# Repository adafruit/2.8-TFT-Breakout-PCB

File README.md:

# 2.8" TFT LCD Display Breakout PCBs
&nbsp; <br />
Click to view/purchase from the Adafruit Shop:
- [2.8" TFT LCD with Touchscreen Breakout Board w/MicroSD Socket - ILI9341](https://www.adafruit.com/product/1770)
- [2.8" 18-bit color TFT LCD with touchscreen breakout board - ILI9325](https://www.adafruit.com/product/335)

Add some jazz & pizazz to your project with a color touchscreen LCD. This TFT display is big (2.8" diagonal) bright (4 white-LED backlight) and colorful! 240x320 pixels with individual RGB pixel control, this has way more resolution than a black and white 128x64 display. As a bonus, this display has a resistive touchscreen attached to it already, so you can detect finger presses anywhere on the screen.

The ILI9325 screen has been discontinued, but the 2.8" ILI341 touchscreen breakout is nearly identical, having both an 8-bit and a SPI interface mode as well as a MicroSD card socket, all in the same form factor! 

Adafruit 2.8" 18-bit color TFT LCD displays with microSD card breakout

These are the Eagle CAD files for the Adafruit 2.8" 18-bit color TFT LCD display with microSD card breakouts:
  ----> https://www.adafruit.com/product/1770 (newer ILI9341 version)
  ----> https://www.adafruit.com/products/335 (older ILI9325 version)

### License

Adafruit invests time and resources providing this open source design, please support Adafruit and open-source hardware by [purchasing products from Adafruit](https://www.adafruit.com)!

All text above must be included in any redistribution

Designed by Limor Fried/Ladyada for Adafruit Industries.
Creative Commons Attribution/Share-Alike, all text above must be included in any redistribution. 
See license.txt for additional information.

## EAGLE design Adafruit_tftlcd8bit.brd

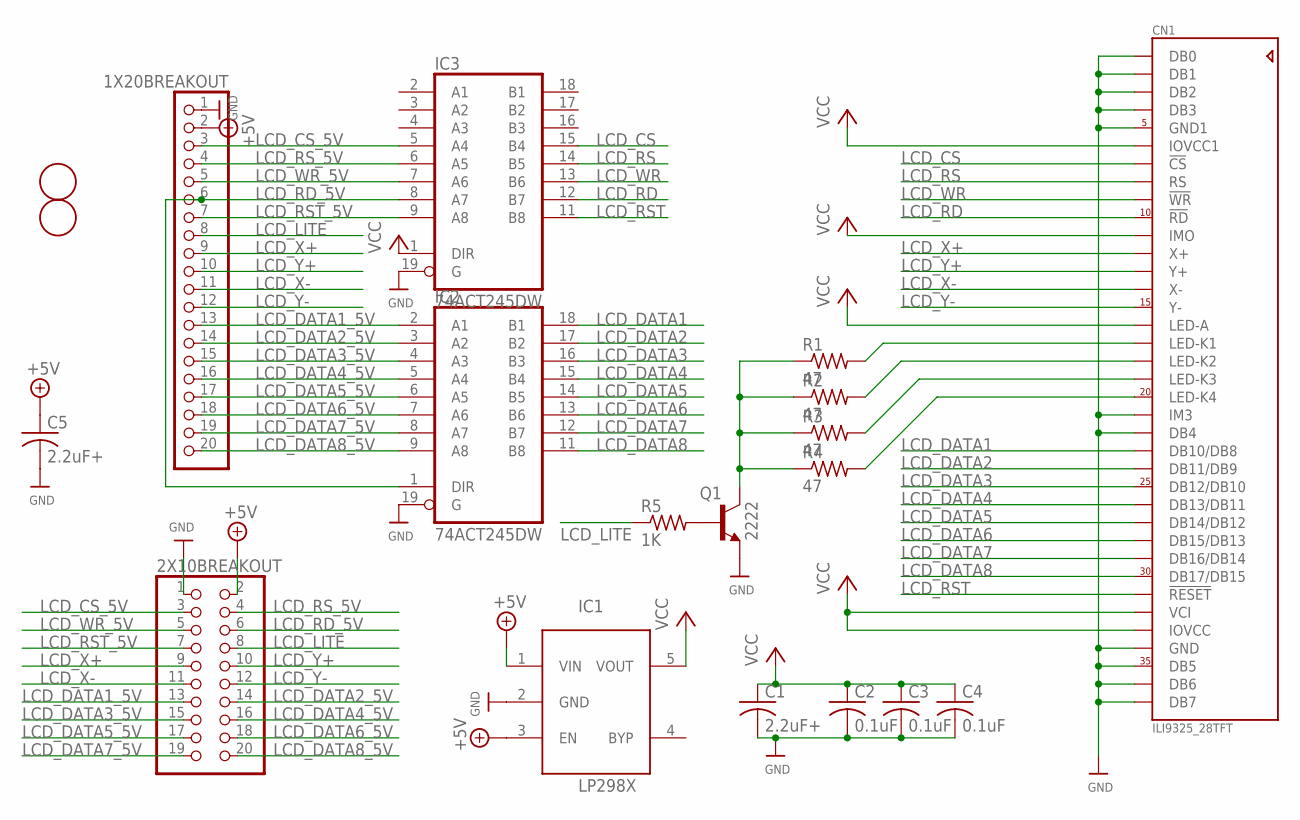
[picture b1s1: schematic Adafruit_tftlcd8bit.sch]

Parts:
1X20BREAKOUT: PINHD-1X20; 1X20
2X10BREAKOUT: PINHD-2X10; 2X10
C1, C5: 2.2uF+; C0805K
C2, C3, C4: 0.1uF; C0805K
CN1: ILI9325_28TFT; ILI9325_28INCH_TS
IC1: LP298XS; SOT23-5L
IC2, IC3: 74ACT245DW; SO20W
Q1: 2222; SOT23-BEC
R1, R2, R3, R4: 47; R0805
R5: 1K; R0805
U$9, U$11: FIDUCIAL; FIDUCIAL_1MM

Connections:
+5V: 1X20BREAKOUT.2, 2X10BREAKOUT.2, C5.1, IC1.1 (VIN), IC1.3 (EN)
GND: 1X20BREAKOUT.1, 2X10BREAKOUT.1, C1.2, C2.2, C3.2, C4.2, C5.2, CN1.1 (DB0), CN1.2 (DB1), CN1.3 (DB2), CN1.4 (DB3), CN1.5 (GND1), CN1.21 (IM3), CN1.22 (DB4), CN1.34 (GND), CN1.35 (DB5), CN1.36 (DB6), CN1.37 (DB7), IC1.2 (GND), IC2.10 (GND), IC2.19 (G), IC3.10 (GND), IC3.19 (G), Q1.E
LCD_CS: CN1.7 (!CS), IC3.15 (B4)
LCD_CS_5V: 1X20BREAKOUT.3, 2X10BREAKOUT.3, IC3.5 (A4)
LCD_DATA1: CN1.23 (DB10/DB8), IC2.18 (B1)
LCD_DATA1_5V: 1X20BREAKOUT.13, 2X10BREAKOUT.13, IC2.2 (A1)
LCD_DATA2: CN1.24 (DB11/DB9), IC2.17 (B2)
LCD_DATA2_5V: 1X20BREAKOUT.14, 2X10BREAKOUT.14, IC2.3 (A2)
LCD_DATA3: CN1.25 (DB12/DB10), IC2.16 (B3)
LCD_DATA3_5V: 1X20BREAKOUT.15, 2X10BREAKOUT.15, IC2.4 (A3)
LCD_DATA4: CN1.26 (DB13/DB11), IC2.15 (B4)
LCD_DATA4_5V: 1X20BREAKOUT.16, 2X10BREAKOUT.16, IC2.5 (A4)
LCD_DATA5: CN1.27 (DB14/DB12), IC2.14 (B5)
LCD_DATA5_5V: 1X20BREAKOUT.17, 2X10BREAKOUT.17, IC2.6 (A5)
LCD_DATA6: CN1.28 (DB15/DB13), IC2.13 (B6)
LCD_DATA6_5V: 1X20BREAKOUT.18, 2X10BREAKOUT.18, IC2.7 (A6)
LCD_DATA7: CN1.29 (DB16/DB14), IC2.12 (B7)
LCD_DATA7_5V: 1X20BREAKOUT.19, 2X10BREAKOUT.19, IC2.8 (A7)
LCD_DATA8: CN1.30 (DB17/DB15), IC2.11 (B8)
LCD_DATA8_5V: 1X20BREAKOUT.20, 2X10BREAKOUT.20, IC2.9 (A8)
LCD_LITE: 1X20BREAKOUT.8, 2X10BREAKOUT.8, R5.1
LCD_RD: CN1.10 (!RD), IC3.12 (B7)
LCD_RD_5V: 1X20BREAKOUT.6, 2X10BREAKOUT.6, IC2.1 (DIR), IC3.8 (A7)
LCD_RS: CN1.8 (RS), IC3.14 (B5)
LCD_RST: CN1.31 (!RESET), IC3.11 (B8)
LCD_RST_5V: 1X20BREAKOUT.7, 2X10BREAKOUT.7, IC3.9 (A8)
LCD_RS_5V: 1X20BREAKOUT.4, 2X10BREAKOUT.4, IC3.6 (A5)
LCD_WR: CN1.9 (!WR), IC3.13 (B6)
LCD_WR_5V: 1X20BREAKOUT.5, 2X10BREAKOUT.5, IC3.7 (A6)
LCD_X+: 1X20BREAKOUT.9, 2X10BREAKOUT.9, CN1.12 (X+)
LCD_X-: 1X20BREAKOUT.11, 2X10BREAKOUT.11, CN1.14 (X-)
LCD_Y+: 1X20BREAKOUT.10, 2X10BREAKOUT.10, CN1.13 (Y+)
LCD_Y-: 1X20BREAKOUT.12, 2X10BREAKOUT.12, CN1.15 (Y-)
unnamed: CN1.20 (LED-K4), R4.2
unnamed: CN1.17 (LED-K1), R1.2
unnamed: CN1.18 (LED-K2), R2.2
unnamed: CN1.19 (LED-K3), R3.2
unnamed: Q1.C, R1.1, R2.1, R3.1, R4.1
unnamed: Q1.B, R5.2
VCC: C1.1, C2.1, C3.1, C4.1, CN1.6 (IOVCC1), CN1.11 (IMO), CN1.16 (LED-A), CN1.32 (VCI), CN1.33 (IOVCC), IC1.5 (VOUT), IC2.20 (VCC), IC3.1 (DIR), IC3.20 (VCC)

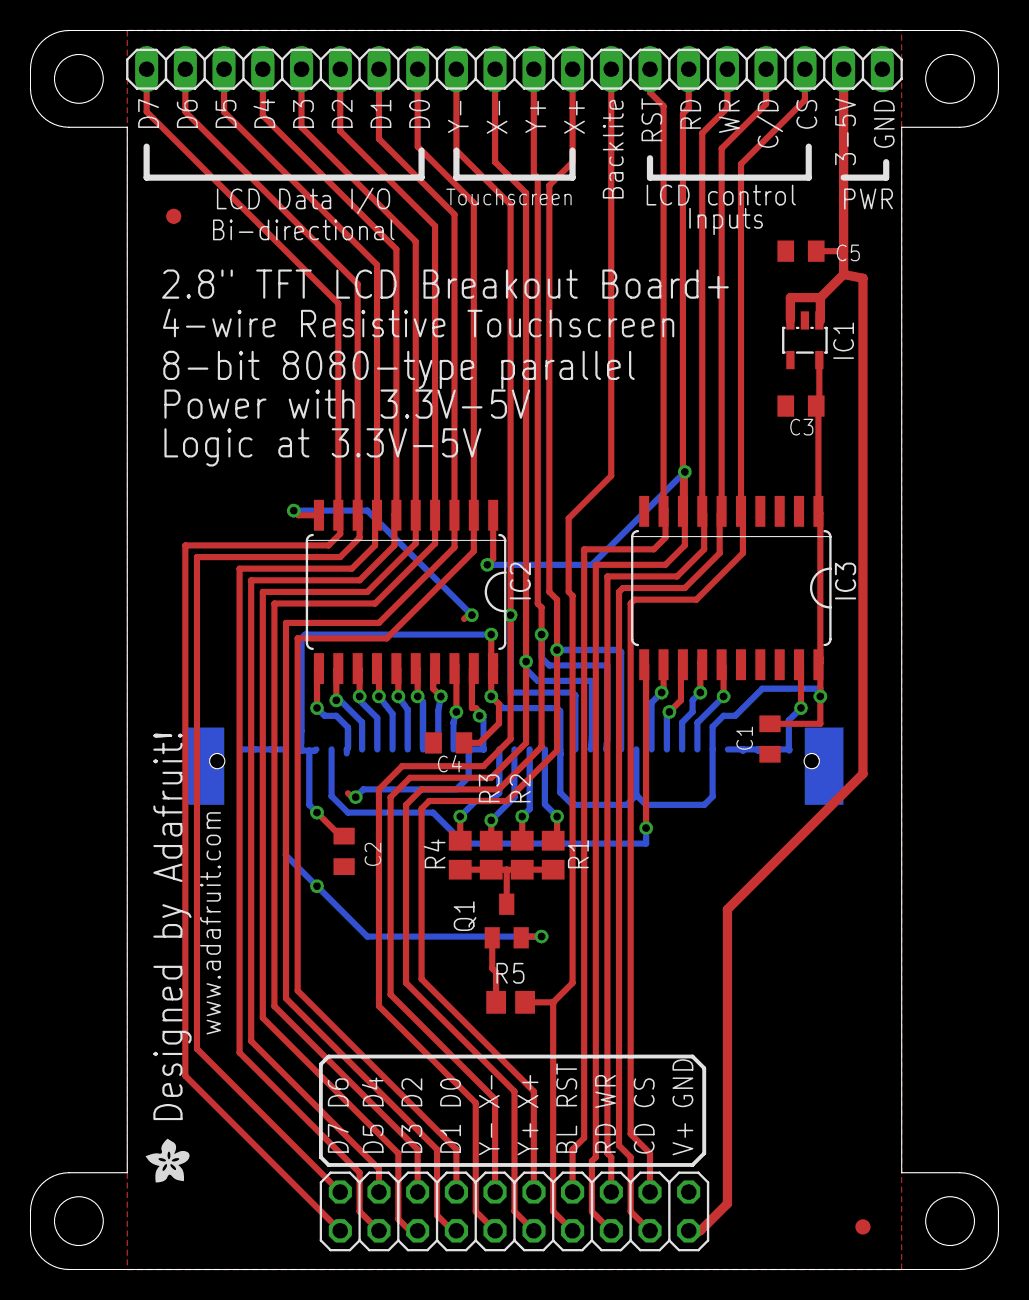
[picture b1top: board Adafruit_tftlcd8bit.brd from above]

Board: 2 copper layers, 63.5 x 81.3 mm, 20 parts (1 on the bottom side), 40 nets.

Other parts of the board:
U$3: ADAFRUIT200MIL

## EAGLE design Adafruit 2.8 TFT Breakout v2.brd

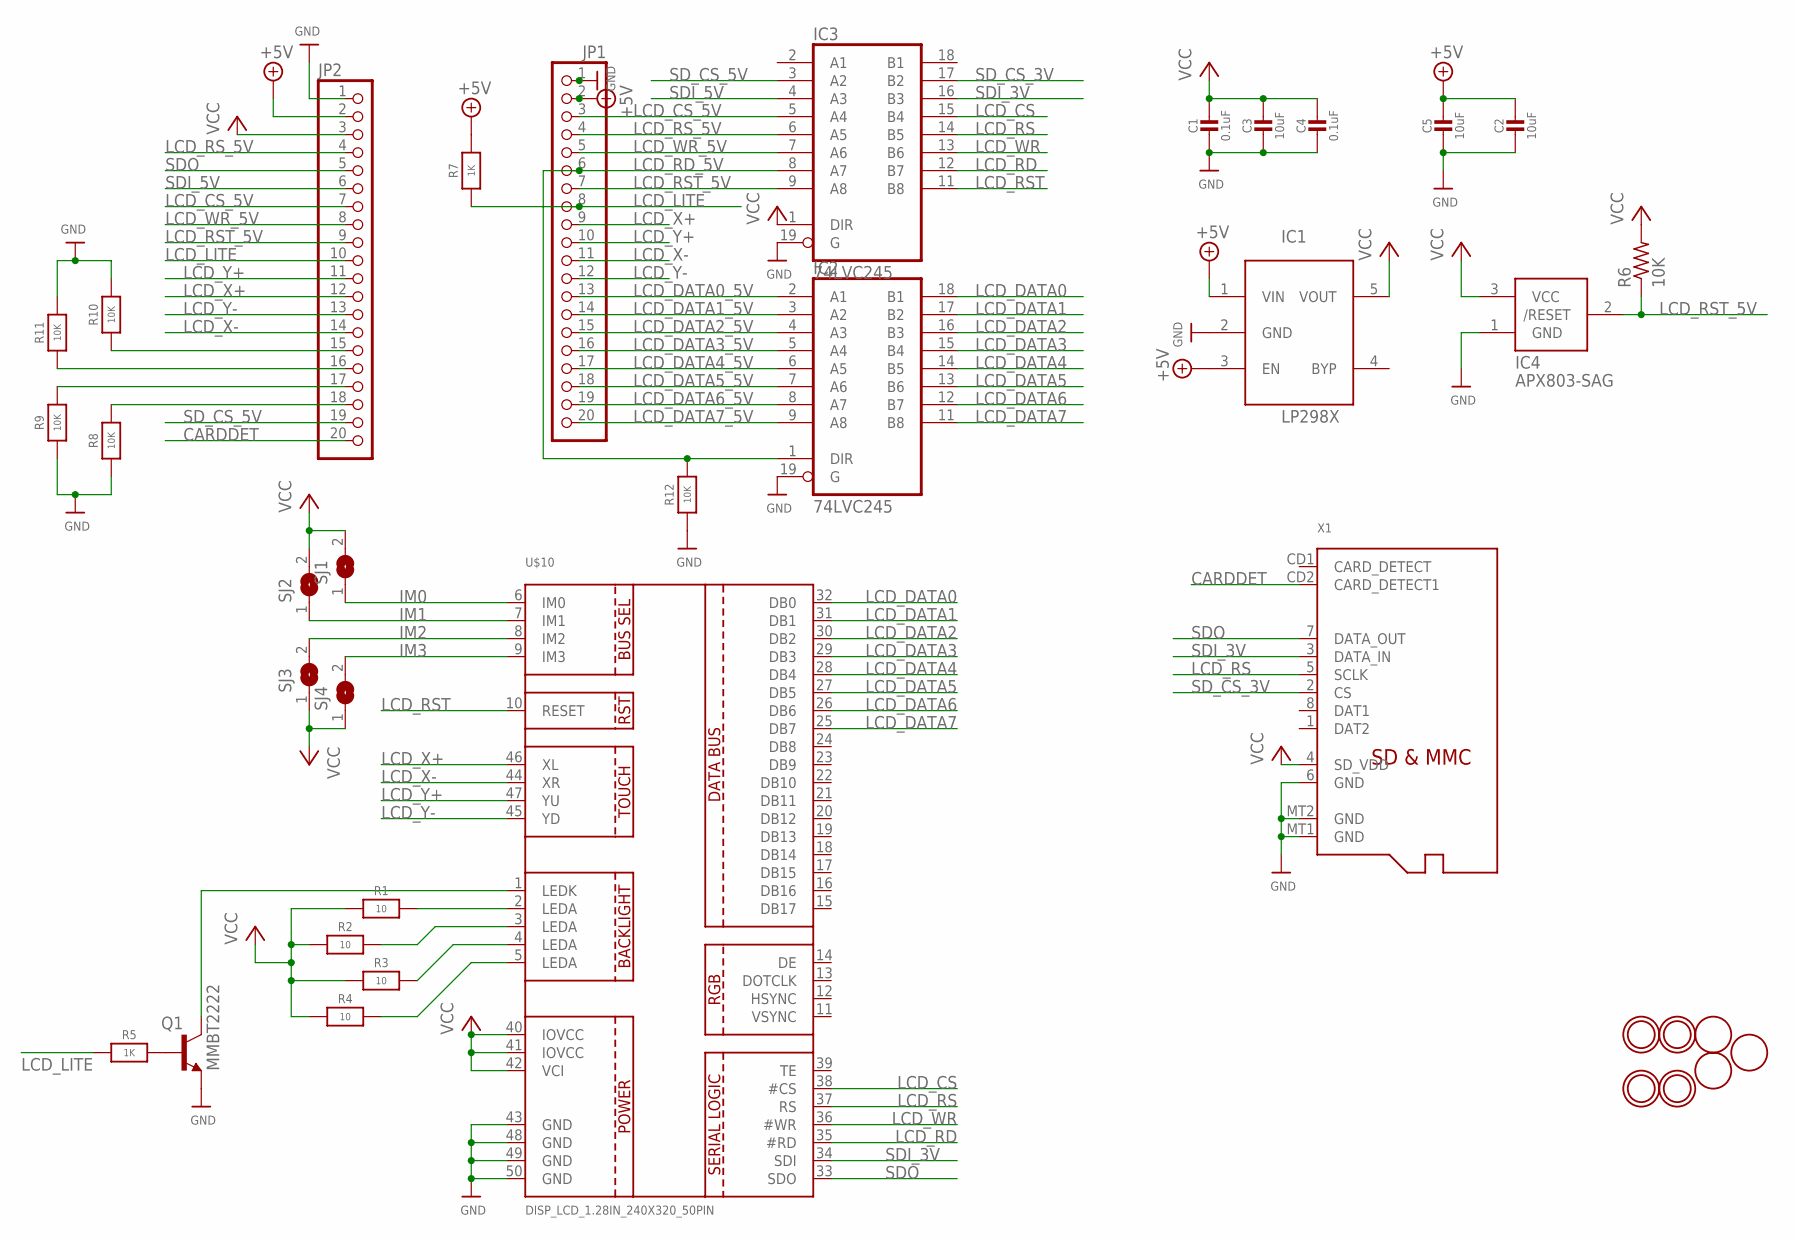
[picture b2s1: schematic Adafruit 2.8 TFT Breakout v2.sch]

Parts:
C1, C4: 0.1uF; 0805-NO
C2, C3, C5: 10uF; 0805-NO
IC1: MIC5225-3.3; SOT23-5L
IC2, IC3: 74LVC245; SO20W
IC4: APX803-SAG; SOT23
JP1, JP2: HEADER-1X20ROUND; 1X20_ROUND
Q1: MMBT2222; SOT23-BEC
R1, R2, R3, R4: 10; 0805-NO
R5, R7: 1K; 0805-NO
R6: 10K; R0805
R8, R9, R10, R11, R12: 10K; 0805-NO
SJ1, SJ2, SJ3, SJ4: SOLDERJUMPER; SOLDERJUMPER_ARROW_NOPASTE
U$7, U$15, U$16, U$17: MOUNTINGHOLE3.0THIN; MOUNTINGHOLE_3.0_PLATEDTHIN
U$9, U$11, U$23: FIDUCIAL; FIDUCIAL_1MM
U$10: DISP_LCD_1.28IN_240X320_50PIN; TFT_2.83IN_240X320_50PIN
X1: MICROSD

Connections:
+5V: C2.1, C5.1, IC1.1 (VIN), IC1.3 (EN), JP1.2, JP2.2, R7.2
CARDDET: JP2.20, X1.CD2 (CARD_DETECT1)
GND: C1.2, C2.2, C3.2, C4.2, C5.2, IC1.2 (GND), IC2.10 (GND), IC2.19 (G), IC3.10 (GND), IC3.19 (G), IC4.1 (GND), JP1.1, JP2.1, Q1.E, R8.1, R9.1, R10.2, R11.2, R12.1, U$10.43 (GND), U$10.48 (GND), U$10.49 (GND), U$10.50 (GND), X1.6 (GND), X1.MT1 (GND), X1.MT2 (GND)
IM0: JP2.18, R8.2, SJ1.1, U$10.6 (IM0)
IM1: JP2.17, R9.2, SJ2.1, U$10.7 (IM1)
IM2: JP2.16, R11.1, SJ3.2, U$10.8 (IM2)
IM3: JP2.15, R10.1, SJ4.2, U$10.9 (IM3)
LCD_CS: IC3.15 (B4), U$10.38 (#CS)
LCD_CS_5V: IC3.5 (A4), JP1.3, JP2.7
LCD_DATA0: IC2.18 (B1), U$10.32 (DB0)
LCD_DATA0_5V: IC2.2 (A1), JP1.13
LCD_DATA1: IC2.17 (B2), U$10.31 (DB1)
LCD_DATA1_5V: IC2.3 (A2), JP1.14
LCD_DATA2: IC2.16 (B3), U$10.30 (DB2)
LCD_DATA2_5V: IC2.4 (A3), JP1.15
LCD_DATA3: IC2.15 (B4), U$10.29 (DB3)
LCD_DATA3_5V: IC2.5 (A4), JP1.16
LCD_DATA4: IC2.14 (B5), U$10.28 (DB4)
LCD_DATA4_5V: IC2.6 (A5), JP1.17
LCD_DATA5: IC2.13 (B6), U$10.27 (DB5)
LCD_DATA5_5V: IC2.7 (A6), JP1.18
LCD_DATA6: IC2.12 (B7), U$10.26 (DB6)
LCD_DATA6_5V: IC2.8 (A7), JP1.19
LCD_DATA7: IC2.11 (B8), U$10.25 (DB7)
LCD_DATA7_5V: IC2.9 (A8), JP1.20
LCD_LITE: JP1.8, JP2.10, R5.1, R7.1
LCD_RD: IC3.12 (B7), U$10.35 (#RD)
LCD_RD_5V: IC2.1 (DIR), IC3.8 (A7), JP1.6, R12.2
LCD_RS: IC3.14 (B5), U$10.37 (RS), X1.5 (SCLK)
LCD_RST: IC3.11 (B8), U$10.10 (RESET)
LCD_RST_5V: IC3.9 (A8), IC4.2 (/RESET), JP1.7, JP2.9, R6.1
LCD_RS_5V: IC3.6 (A5), JP1.4, JP2.4
LCD_WR: IC3.13 (B6), U$10.36 (#WR)
LCD_WR_5V: IC3.7 (A6), JP1.5, JP2.8
LCD_X+: JP1.9, JP2.12, U$10.46 (XL)
LCD_X-: JP1.11, JP2.14, U$10.44 (XR)
LCD_Y+: JP1.10, JP2.11, U$10.47 (YU)
LCD_Y-: JP1.12, JP2.13, U$10.45 (YD)
unnamed: R4.2, U$10.5 (LEDA)
unnamed: R1.2, U$10.2 (LEDA)
unnamed: R2.2, U$10.3 (LEDA)
unnamed: R3.2, U$10.4 (LEDA)
unnamed: Q1.C, U$10.1 (LEDK)
unnamed: Q1.B, R5.2
SDI_3V: IC3.16 (B3), U$10.34 (SDI), X1.3 (DATA_IN)
SDI_5V: IC3.4 (A3), JP2.6
SDO: JP2.5, U$10.33 (SDO), X1.7 (DATA_OUT)
SD_CS_3V: IC3.17 (B2), X1.2 (CS)
SD_CS_5V: IC3.3 (A2), JP2.19
VCC: C1.1, C3.1, C4.1, IC1.5 (VOUT), IC2.20 (VCC), IC3.1 (DIR), IC3.20 (VCC), IC4.3 (VCC), JP2.3, R1.1, R2.1, R3.1, R4.1, R6.2, SJ1.2, SJ2.2, SJ3.1, SJ4.1, U$10.40 (IOVCC), U$10.41 (IOVCC), U$10.42 (VCI), X1.4 (SD_VDD)

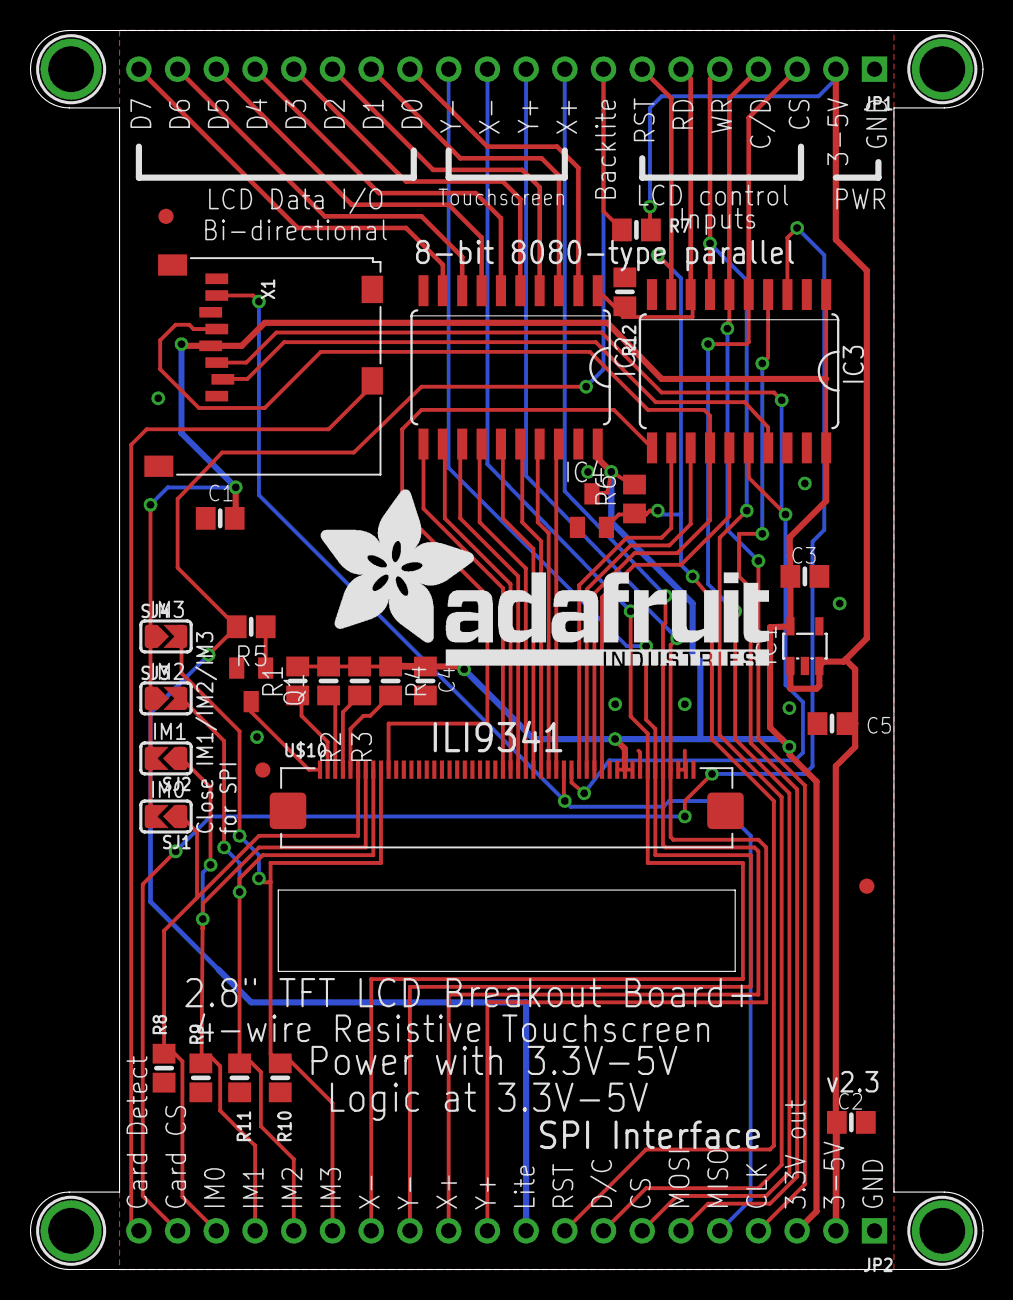
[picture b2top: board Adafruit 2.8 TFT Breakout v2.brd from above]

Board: 2 copper layers, 62.5 x 81.3 mm, 38 parts (1 on the bottom side), 50 nets.

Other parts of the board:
U$19: ADAFRUIT_TEXT_30MM

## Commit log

2012-04-19 Eagle Cad files!
2014-10-03 new v2 + readme
2026-06-03 update file format to XML
